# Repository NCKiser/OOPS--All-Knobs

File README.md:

# OOPS! All Encoders
A 19mm (Planck) spaced 4x12 PCB that has the option for an encoder in every switch position.
Runs on an rp2040. Should fit in most Planck cases low-, mid-, or high-profile.
There is currently no license for this work. Do not distribute or monetize without approval from Noah Kiser.

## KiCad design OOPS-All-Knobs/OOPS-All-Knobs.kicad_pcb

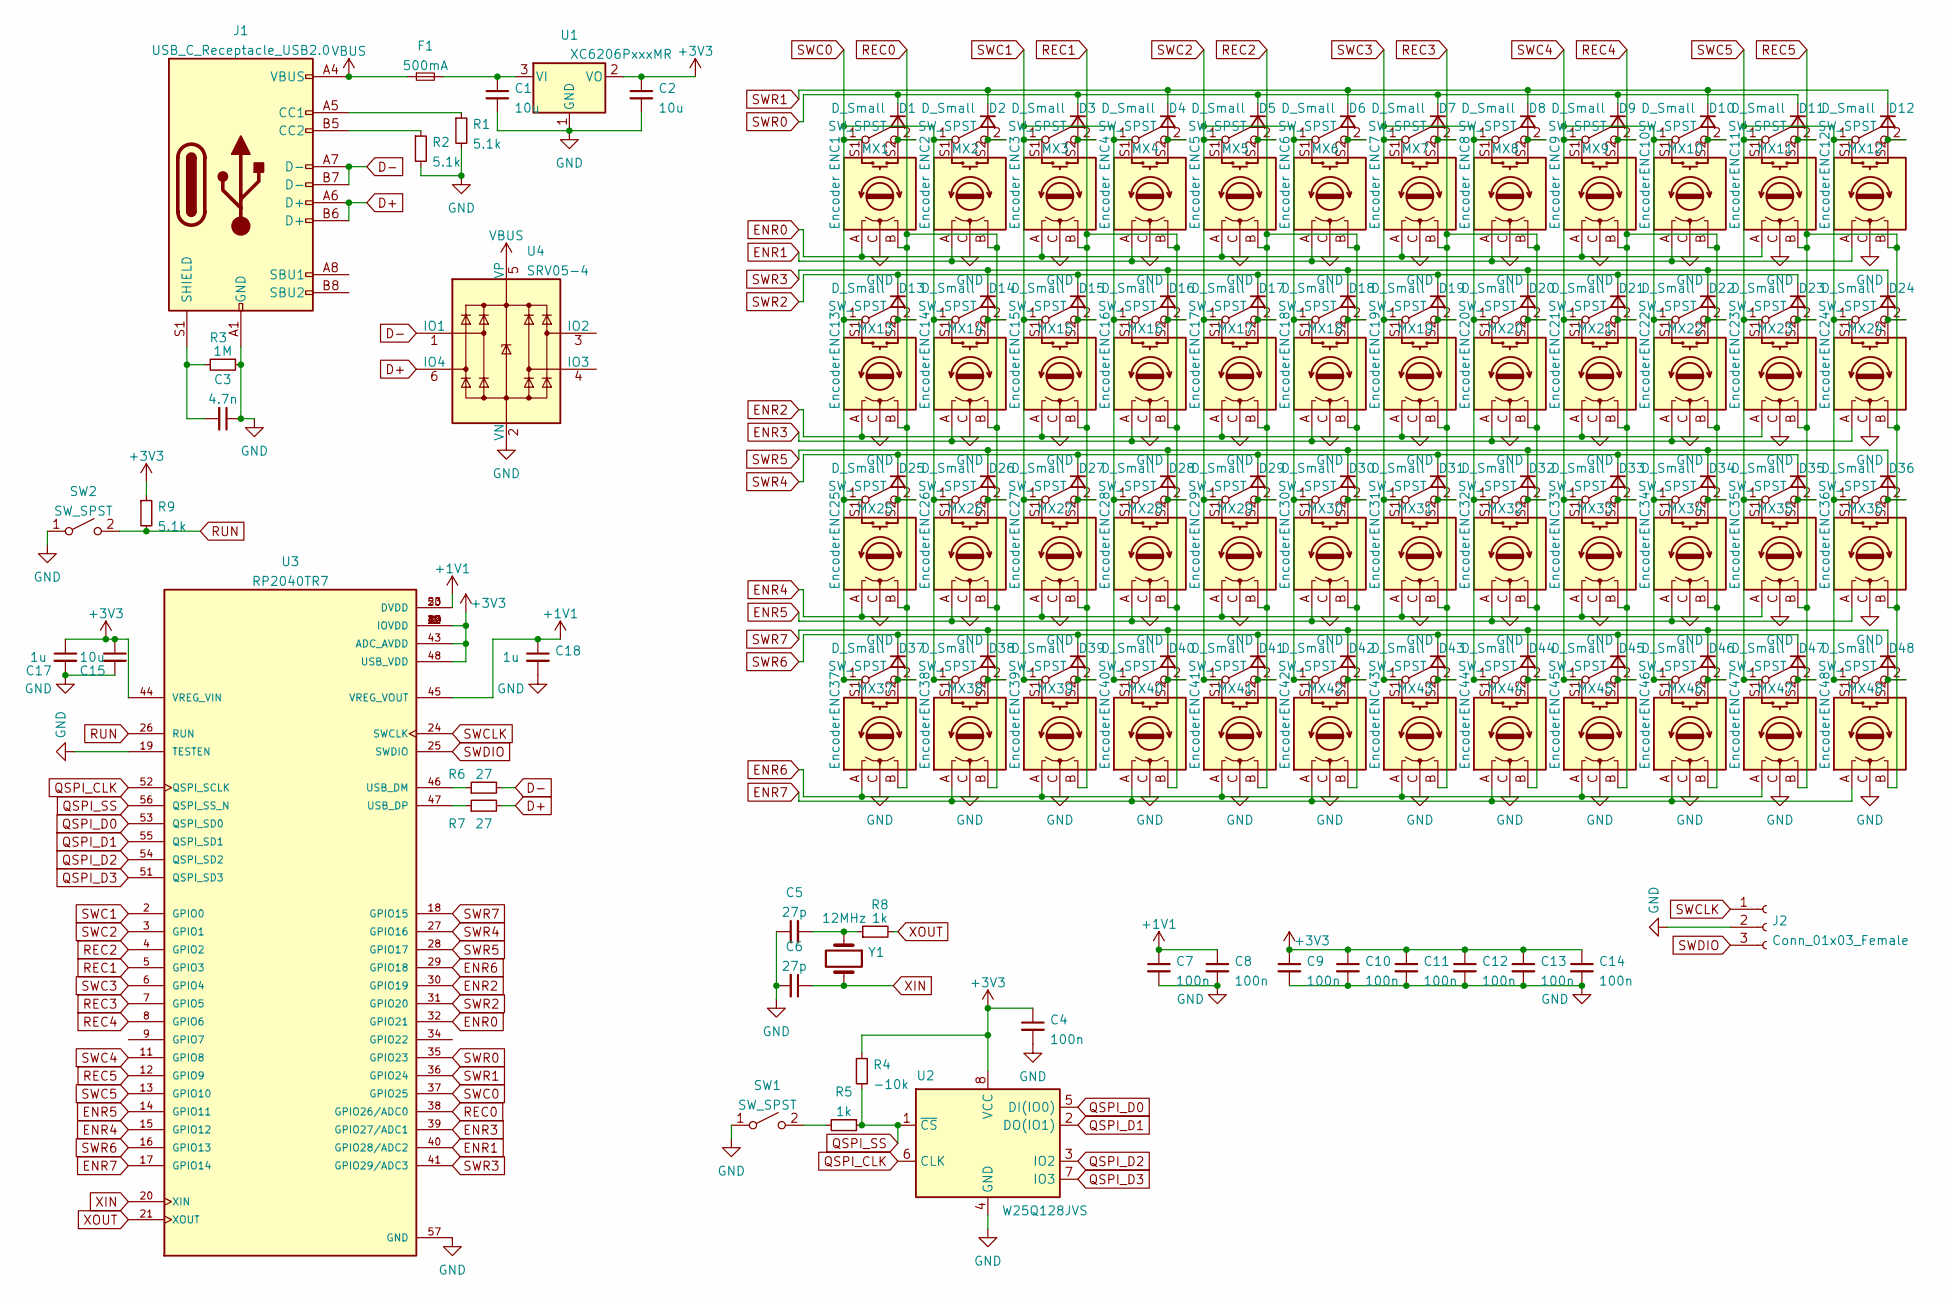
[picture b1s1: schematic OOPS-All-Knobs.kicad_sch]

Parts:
C1, C2, C15: 10u; C_0402_1005Metric
C3: 4.7n; C_0402_1005Metric
C4, C7, C8, C9, C10, C11, C12, C13, C14: 100n; C_0402_1005Metric
C5, C6: 27p; C_0402_1005Metric
C17, C18: 1u; C_0402_1005Metric
D1, D2, D3, D4, D5, D6, D7, D8, D9, D10, D11, D12, D13, D14, D15, D16, D17, D18, D19, D20, D21, D22, D23, D24, D25, D26, D27, D28, D29, D30, D31, D32, D33, D34, D35, D36, D37, D38, D39, D40, D41, D42, D43, D44, D45, D46, D47, D48: D_Small; D_SOD-123
ENC1, ENC2, ENC3, ENC4, ENC5, ENC6, ENC7, ENC8, ENC9, ENC10, ENC11, ENC12, ENC13, ENC14, ENC15, ENC16, ENC17, ENC18, ENC19, ENC20, ENC21, ENC22, ENC23, ENC24, ENC25, ENC26, ENC27, ENC28, ENC29, ENC30, ENC31, ENC32, ENC33, ENC34, ENC35, ENC36, ENC37, ENC38, ENC39, ENC40, ENC41, ENC42, ENC43, ENC44, ENC45, ENC46, ENC47, ENC48: Encoder; RotaryEncoder_Alps_EC11E-Switch_Vertical_H20mm
F1: 500mA; Fuse_1206_3216Metric
J1: USB_C_Receptacle_USB2.0; USB_C_Receptacle_HRO_TYPE-C-31-M-12
J2: Conn_01x03_Female; PinHeader_1x03_P2.54mm_Vertical
MX1, MX2, MX3, MX4, MX5, MX6, MX7, MX8, MX9, MX10, MX11, MX12, MX13, MX14, MX15, MX16, MX17, MX18, MX19, MX20, MX21, MX22, MX23, MX24, MX25, MX26, MX27, MX28, MX29, MX30, MX31, MX32, MX33, MX34, MX35, MX36, MX37, MX38, MX39, MX40, MX41, MX42, MX43, MX44, MX45, MX46, MX47, MX48: SW_SPST; MXOnly-1U-NoLED
R1, R2, R9: 5.1k; R_0402_1005Metric
R3: 1M; R_0402_1005Metric
R4: -10k; R_0603_1608Metric
R5, R8: 1k; R_0402_1005Metric
R6, R7: 27; R_0402_1005Metric
SW1, SW2: SW_SPST; SW_SPST_TL3342
U1: XC6206PxxxMR; SOT-23
U2: W25Q128JVS; SOIC-8_5.23x5.23mm_P1.27mm
U3: RP2040TR7; QFN40P700X700X90-57N; PARTREV 1.7.1
U4: SRV05-4; SOT-23-6-routable
Y1: 12MHz; Crystal_SMD_3225-4Pin_3.2x2.5mm

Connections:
+1V1: C7.1, C8.1, C18.1, U3.23 (DVDD), U3.45 (VREG_VOUT), U3.50 (DVDD)
+3V3: C2.1, C4.1, C9.1, C10.1, C11.1, C12.1, C13.1, C14.1, C15.1, C17.1, R4.1, R9.1, U1.2 (VO), U2.8 (VCC), U3.1 (IOVDD), U3.10 (IOVDD), U3.22 (IOVDD), U3.33 (IOVDD), U3.42 (IOVDD), U3.43 (ADC_AVDD), U3.44 (VREG_VIN), U3.48 (USB_VDD), U3.49 (IOVDD)
D+: J1.A6 (D+), J1.B6 (D+), R7.2, U4.6 (IO4)
D-: J1.A7 (D-), J1.B7 (D-), R6.2, U4.1 (IO1)
ENR0: ENC1.A, ENC3.A, ENC5.A, ENC7.A, ENC9.A, ENC11.A, U3.32 (GPIO21)
ENR1: ENC2.A, ENC4.A, ENC6.A, ENC8.A, ENC10.A, ENC12.A, U3.40 (GPIO28/ADC2)
ENR2: ENC13.A, ENC15.A, ENC17.A, ENC19.A, ENC21.A, ENC23.A, U3.30 (GPIO19)
ENR3: ENC14.A, ENC16.A, ENC18.A, ENC20.A, ENC22.A, ENC24.A, U3.39 (GPIO27/ADC1)
ENR4: ENC25.A, ENC27.A, ENC29.A, ENC31.A, ENC33.A, ENC35.A, U3.15 (GPIO12)
ENR5: ENC26.A, ENC28.A, ENC30.A, ENC32.A, ENC34.A, ENC36.A, U3.14 (GPIO11)
ENR6: ENC37.A, ENC39.A, ENC41.A, ENC43.A, ENC45.A, ENC47.A, U3.29 (GPIO18)
ENR7: ENC38.A, ENC40.A, ENC42.A, ENC44.A, ENC46.A, ENC48.A, U3.17 (GPIO14)
GND: C1.2, C2.2, C3.1, C4.2, C5.1, C6.2, C7.2, C8.2, C9.2, C10.2, C11.2, C12.2, C13.2, C14.2, C15.2, C17.2, C18.2, ENC1.C, ENC2.C, ENC3.C, ENC4.C, ENC5.C, ENC6.C, ENC7.C, ENC8.C, ENC9.C, ENC10.C, ENC11.C, ENC12.C, ENC13.C, ENC14.C, ENC15.C, ENC16.C, ENC17.C, ENC18.C, ENC19.C, ENC20.C, ENC21.C, ENC22.C, ENC23.C, ENC24.C, ENC25.C, ENC26.C, ENC27.C, ENC28.C, ENC29.C, ENC30.C, ENC31.C, ENC32.C, ENC33.C, ENC34.C, ENC35.C, ENC36.C, ENC37.C, ENC38.C, ENC39.C, ENC40.C, ENC41.C, ENC42.C, ENC43.C, ENC44.C, ENC45.C, ENC46.C, ENC47.C, ENC48.C, J1.A1 (GND), J1.A12 (GND), J1.B1 (GND), J1.B12 (GND), J2.2, R1.2, R2.2, R3.1, SW1.1 (A), SW2.1 (A), U1.1 (GND), U2.4 (GND), U3.19 (TESTEN), U3.57 (GND), U4.2 (VN)
unnamed: C1.1, F1.2, U1.3 (VI)
unnamed: C3.2, J1.S1 (SHIELD), R3.2
unnamed: C5.2, R8.1, Y1.1
unnamed: D1.2 (A), ENC1.S2, MX1.2 (B)
unnamed: D2.2 (A), ENC2.S2, MX2.2 (B)
unnamed: D3.2 (A), ENC3.S2, MX3.2 (B)
unnamed: D4.2 (A), ENC4.S2, MX4.2 (B)
unnamed: D5.2 (A), ENC5.S2, MX5.2 (B)
unnamed: D6.2 (A), ENC6.S2, MX6.2 (B)
unnamed: D7.2 (A), ENC7.S2, MX7.2 (B)
unnamed: D8.2 (A), ENC8.S2, MX8.2 (B)
unnamed: D9.2 (A), ENC9.S2, MX9.2 (B)
unnamed: D10.2 (A), ENC10.S2, MX10.2 (B)
unnamed: D11.2 (A), ENC11.S2, MX11.2 (B)
unnamed: D12.2 (A), ENC12.S2, MX12.2 (B)
unnamed: D13.2 (A), ENC13.S2, MX13.2 (B)
unnamed: D14.2 (A), ENC14.S2, MX14.2 (B)
unnamed: D15.2 (A), ENC15.S2, MX15.2 (B)
unnamed: D16.2 (A), ENC16.S2, MX16.2 (B)
unnamed: D17.2 (A), ENC17.S2, MX17.2 (B)
unnamed: D18.2 (A), ENC18.S2, MX18.2 (B)
unnamed: D19.2 (A), ENC19.S2, MX19.2 (B)
unnamed: D20.2 (A), ENC20.S2, MX20.2 (B)
unnamed: D21.2 (A), ENC21.S2, MX21.2 (B)
unnamed: D22.2 (A), ENC22.S2, MX22.2 (B)
unnamed: D23.2 (A), ENC23.S2, MX23.2 (B)
unnamed: D24.2 (A), ENC24.S2, MX24.2 (B)
unnamed: D25.2 (A), ENC25.S2, MX25.2 (B)
unnamed: D26.2 (A), ENC26.S2, MX26.2 (B)
unnamed: D27.2 (A), ENC27.S2, MX27.2 (B)
unnamed: D28.2 (A), ENC28.S2, MX28.2 (B)
unnamed: D29.2 (A), ENC29.S2, MX29.2 (B)
unnamed: D30.2 (A), ENC30.S2, MX30.2 (B)
unnamed: D31.2 (A), ENC31.S2, MX31.2 (B)
unnamed: D32.2 (A), ENC32.S2, MX32.2 (B)
unnamed: D33.2 (A), ENC33.S2, MX33.2 (B)
unnamed: D34.2 (A), ENC34.S2, MX34.2 (B)
unnamed: D35.2 (A), ENC35.S2, MX35.2 (B)
unnamed: D36.2 (A), ENC36.S2, MX36.2 (B)
unnamed: D37.2 (A), ENC37.S2, MX37.2 (B)
unnamed: D38.2 (A), ENC38.S2, MX38.2 (B)
unnamed: D39.2 (A), ENC39.S2, MX39.2 (B)
unnamed: D40.2 (A), ENC40.S2, MX40.2 (B)
unnamed: D41.2 (A), ENC41.S2, MX41.2 (B)
unnamed: D42.2 (A), ENC42.S2, MX42.2 (B)
unnamed: D43.2 (A), ENC43.S2, MX43.2 (B)
unnamed: D44.2 (A), ENC44.S2, MX44.2 (B)
unnamed: D45.2 (A), ENC45.S2, MX45.2 (B)
unnamed: D46.2 (A), ENC46.S2, MX46.2 (B)
unnamed: D47.2 (A), ENC47.S2, MX47.2 (B)
unnamed: D48.2 (A), ENC48.S2, MX48.2 (B)
unnamed: J1.A5 (CC1), R1.1
unnamed: J1.B5 (CC2), R2.1
unnamed: R5.2, SW1.2 (B)
unnamed: R6.1, U3.46 (USB_DM)
unnamed: R7.1, U3.47 (USB_DP)
QSPI_CLK: U2.6 (CLK), U3.52 (QSPI_SCLK)
QSPI_D0: U2.5 (DI(IO0)), U3.53 (QSPI_SD0)
QSPI_D1: U2.2 (DO(IO1)), U3.55 (QSPI_SD1)
QSPI_D2: U2.3 (IO2), U3.54 (QSPI_SD2)
QSPI_D3: U2.7 (IO3), U3.51 (QSPI_SD3)
QSPI_SS: R4.2, R5.1, U2.1 (~CS), U3.56 (QSPI_SS_N)
REC0: ENC1.B, ENC2.B, ENC13.B, ENC14.B, ENC25.B, ENC26.B, ENC37.B, ENC38.B, U3.38 (GPIO26/ADC0)
REC1: ENC3.B, ENC4.B, ENC15.B, ENC16.B, ENC27.B, ENC28.B, ENC39.B, ENC40.B, U3.5 (GPIO3)
REC2: ENC5.B, ENC6.B, ENC17.B, ENC18.B, ENC29.B, ENC30.B, ENC41.B, ENC42.B, U3.4 (GPIO2)
REC3: ENC7.B, ENC8.B, ENC19.B, ENC20.B, ENC31.B, ENC32.B, ENC43.B, ENC44.B, U3.7 (GPIO5)
REC4: ENC9.B, ENC10.B, ENC21.B, ENC22.B, ENC33.B, ENC34.B, ENC45.B, ENC46.B, U3.8 (GPIO6)
REC5: ENC11.B, ENC12.B, ENC23.B, ENC24.B, ENC35.B, ENC36.B, ENC47.B, ENC48.B, U3.12 (GPIO9)
RUN: R9.2, SW2.2 (B), U3.26 (RUN)
SWC0: ENC1.S1, ENC2.S1, ENC13.S1, ENC14.S1, ENC25.S1, ENC26.S1, ENC37.S1, ENC38.S1, MX1.1 (A), MX2.1 (A), MX13.1 (A), MX14.1 (A), MX25.1 (A), MX26.1 (A), MX37.1 (A), MX38.1 (A), U3.37 (GPIO25)
SWC1: ENC3.S1, ENC4.S1, ENC15.S1, ENC16.S1, ENC27.S1, ENC28.S1, ENC39.S1, ENC40.S1, MX3.1 (A), MX4.1 (A), MX15.1 (A), MX16.1 (A), MX27.1 (A), MX28.1 (A), MX39.1 (A), MX40.1 (A), U3.2 (GPIO0)
SWC2: ENC5.S1, ENC6.S1, ENC17.S1, ENC18.S1, ENC29.S1, ENC30.S1, ENC41.S1, ENC42.S1, MX5.1 (A), MX6.1 (A), MX17.1 (A), MX18.1 (A), MX29.1 (A), MX30.1 (A), MX41.1 (A), MX42.1 (A), U3.3 (GPIO1)
SWC3: ENC7.S1, ENC8.S1, ENC19.S1, ENC20.S1, ENC31.S1, ENC32.S1, ENC43.S1, ENC44.S1, MX7.1 (A), MX8.1 (A), MX19.1 (A), MX20.1 (A), MX31.1 (A), MX32.1 (A), MX43.1 (A), MX44.1 (A), U3.6 (GPIO4)
SWC4: ENC9.S1, ENC10.S1, ENC21.S1, ENC22.S1, ENC33.S1, ENC34.S1, ENC45.S1, ENC46.S1, MX9.1 (A), MX10.1 (A), MX21.1 (A), MX22.1 (A), MX33.1 (A), MX34.1 (A), MX45.1 (A), MX46.1 (A), U3.11 (GPIO8)
SWC5: ENC11.S1, ENC12.S1, ENC23.S1, ENC24.S1, ENC35.S1, ENC36.S1, ENC47.S1, ENC48.S1, MX11.1 (A), MX12.1 (A), MX23.1 (A), MX24.1 (A), MX35.1 (A), MX36.1 (A), MX47.1 (A), MX48.1 (A), U3.13 (GPIO10)
SWCLK: J2.1, U3.24 (SWCLK)
SWDIO: J2.3, U3.25 (SWDIO)
SWR0: D1.1 (K), D3.1 (K), D5.1 (K), D7.1 (K), D9.1 (K), D11.1 (K), U3.35 (GPIO23)
SWR1: D2.1 (K), D4.1 (K), D6.1 (K), D8.1 (K), D10.1 (K), D12.1 (K), U3.36 (GPIO24)
SWR2: D13.1 (K), D15.1 (K), D17.1 (K), D19.1 (K), D21.1 (K), D23.1 (K), U3.31 (GPIO20)
SWR3: D14.1 (K), D16.1 (K), D18.1 (K), D20.1 (K), D22.1 (K), D24.1 (K), U3.41 (GPIO29/ADC3)
SWR4: D25.1 (K), D27.1 (K), D29.1 (K), D31.1 (K), D33.1 (K), D35.1 (K), U3.27 (GPIO16)
SWR5: D26.1 (K), D28.1 (K), D30.1 (K), D32.1 (K), D34.1 (K), D36.1 (K), U3.28 (GPIO17)
SWR6: D37.1 (K), D39.1 (K), D41.1 (K), D43.1 (K), D45.1 (K), D47.1 (K), U3.16 (GPIO13)
SWR7: D38.1 (K), D40.1 (K), D42.1 (K), D44.1 (K), D46.1 (K), D48.1 (K), U3.18 (GPIO15)
VBUS: F1.1, J1.A4 (VBUS), J1.A9 (VBUS), J1.B4 (VBUS), J1.B9 (VBUS), U4.5 (VP)
XIN: C6.1, U3.20 (XIN), Y1.2
XOUT: R8.2, U3.21 (XOUT)

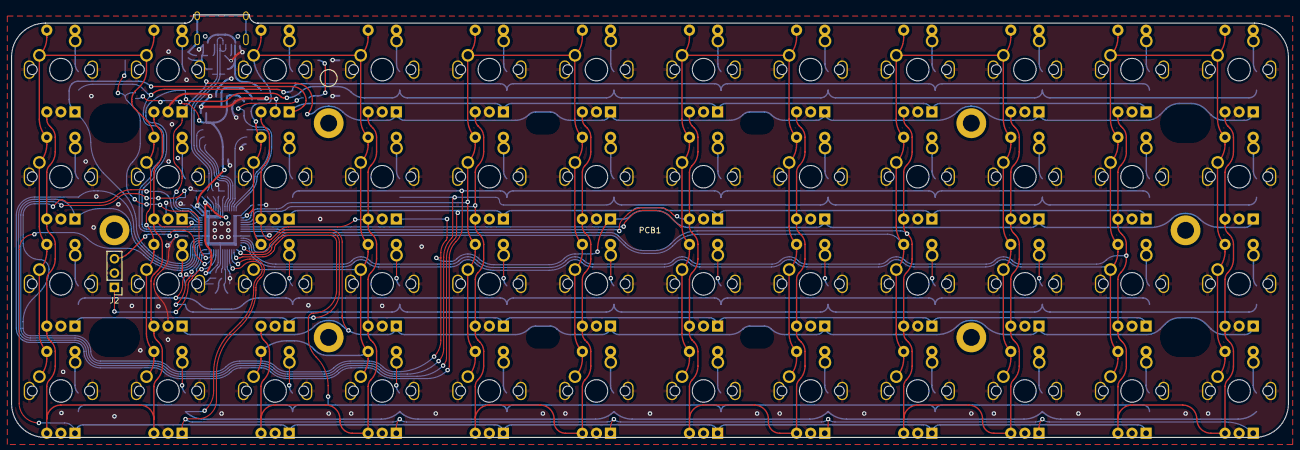
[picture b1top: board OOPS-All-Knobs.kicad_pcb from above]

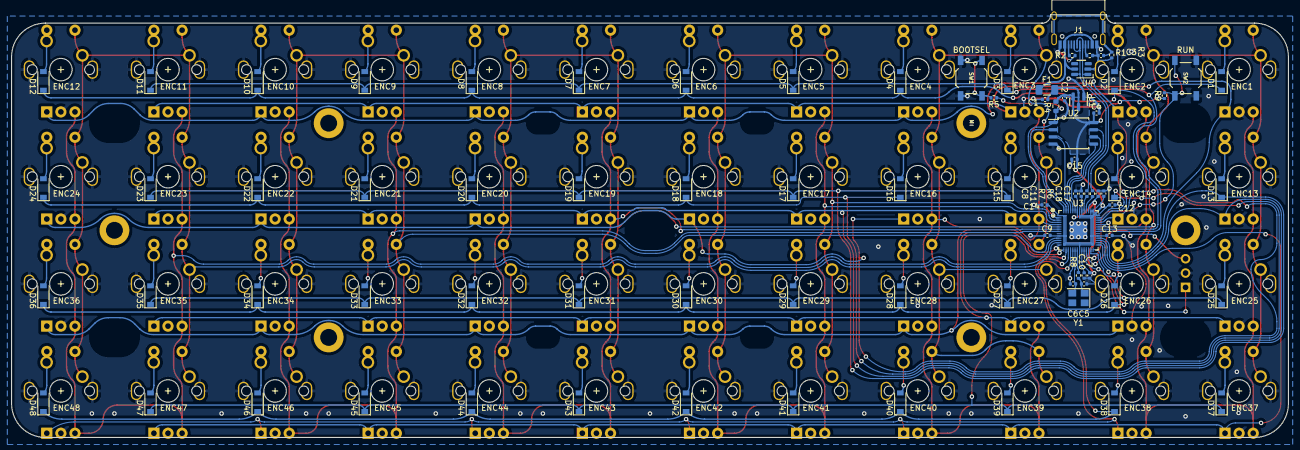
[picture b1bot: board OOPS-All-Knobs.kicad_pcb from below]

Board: 2 copper layers, 226.5 x 75.0 mm, 181 parts (131 on the bottom side), 101 nets.

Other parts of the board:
PCB1: planck-pcb-module

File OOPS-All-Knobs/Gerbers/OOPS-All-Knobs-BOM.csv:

Comment,Designator,Footprint,LCSC Part Number,Quantity
D_Small,"D44,D9,D28,D4,D1,D23,D45,D43,D38,D16,D11,D26,D13,D39,D5,D19,D22,D36,D27,D21,D14,D37,D30,D35,D10,D12,D18,D34,D3,D48,D31,D42,D32,D25,D24,D41,D40,D8,D47,D33,D20,D29,D2,D15,D17,D6,D7,D46",D_SOD-123,C81598,48
100n,"C10,C14,C4,C8,C12,C11,C13,C9,C7",C_0402_1005Metric,C307331,9
1M,R3,R_0402_1005Metric,C26083,1
1k,"R8,R5",R_0402_1005Metric,C11702,2
27p,"C6,C5",C_0402_1005Metric,C1557,2
XC6206-3.3_SOT23,U1,SOT-23,C5446,1
SW_SPST,"SW1,SW2",SW_SPST_TL3342,C318884,2
500mA,F1,Fuse_1206_3216Metric,C70076,1
12MHz,Y1,Crystal_SMD_3225-4Pin_3.2x2.5mm,,1
27,"R6,R7",R_0402_1005Metric,C25092,2
W25Q128JVS,U2,SOIC-8_5.23x5.23mm_P1.27mm,C97521,1
USB_C_Receptacle_USB2.0,J1,USB_C_Receptacle_HRO_TYPE-C-31-M-12,C165948,1
5.1k,"R2,R9,R1",R_0402_1005Metric,C25905,3
10u,"C1,C2,C15",C_0402_1005Metric,C15525,3
1u,"C18,C17",C_0402_1005Metric,C52923,2
SRV05-4,U4,SOT-23-6-routable,C85364,1
-10k,R4,R_0603_1608Metric,,1
RP2040TR7,U3,QFN40P700X700X90-57N,C2040,1
4.7n,C3,C_0402_1005Metric,C1538,1

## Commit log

2022-03-09 initial matrix
2022-03-09 Added ground
2022-03-09 Added Planck footprint
2022-03-10 Placed and routed controller
2022-03-12 Some progress on routing matrices
2022-03-12 routed controller, just a few connections left
2022-03-13 More ground stitching, pics and schematic
2022-03-13 Implemented proposed fixes for testgen, shielding, and xtal
2022-03-13 a few more improvements
2022-03-24 Gerbers ready for manu
2022-03-24 Everything but the crystal
2022-03-25 Ready for Manu!
2022-04-13 change encoder footprints
2022-04-14 Added 2u positions, needs routing
2022-11-08 backups
